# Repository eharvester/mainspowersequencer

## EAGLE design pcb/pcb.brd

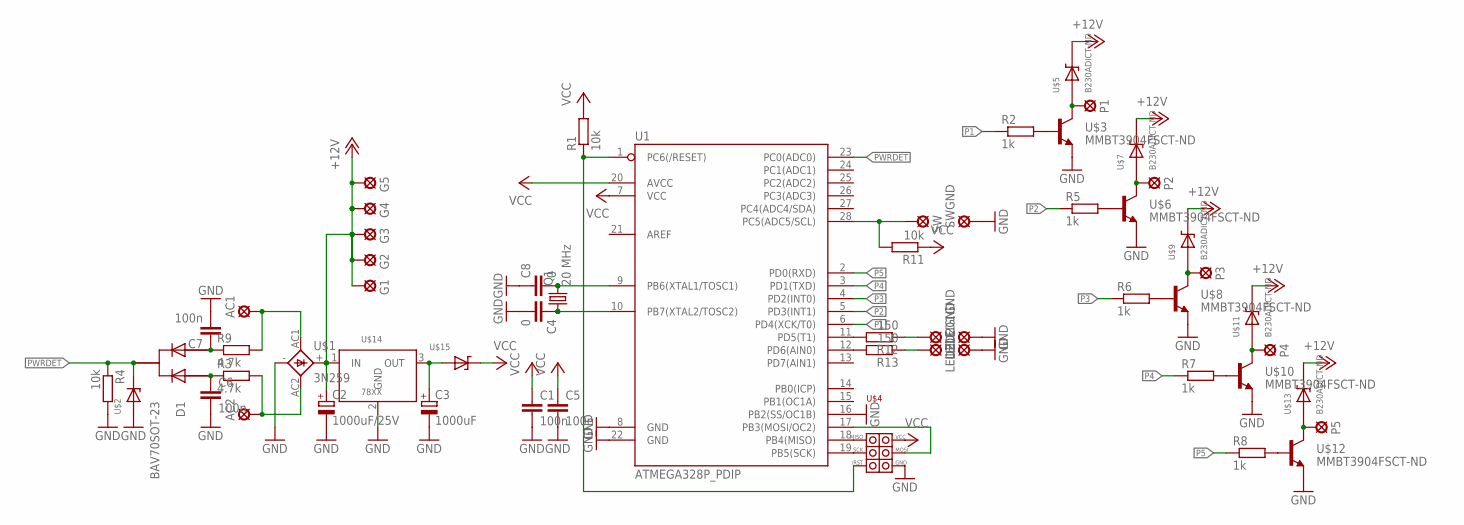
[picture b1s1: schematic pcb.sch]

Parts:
AC1, AC2: LSP10
C1, C5, C6, C7: 100n; C0603
C2: 1000uF/25V; E5-13
C3: 1000uF; E5-10,5
C4, C8: 0; C0603
D1: BAV70SOT-23; SOT23
G1, G2, G3, G4, G5: LSP10
LED1, LED1GND, LED2, LED2GND: LSP10
P1, P2, P3, P4, P5: LSP10
Q1: 20 MHz; CTS406
R1, R4, R11: 10k; R0603
R2, R5, R6, R7, R8: 1k; R0603
R3, R9: 4.7k; R0603
R12, R13: 150; R0603
SW: LSP10
SWGND: LSP10
U1: ATMEGA328P_PDIP; DIL28-3
U$1: 3N259; KBPM
U$2: MA8051CT; SOD323-W
U$3, U$6, U$8, U$10, U$12: MMBT3904FSCT-ND; SOT-23
U$4: ISP-HEADER-6; ISPHEADER-6
U$5, U$7, U$9, U$11, U$13: B230ADICT-ND; SMA/SMB
U$14: 78XX; DPAK
U$15: MBRM140T1; CASE457

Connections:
+12V: C2.+, G1.MP, G2.MP, G3.MP, G4.MP, G5.MP, U$1.+, U$5.1 (CAT), U$7.1 (CAT), U$9.1 (CAT), U$11.1 (CAT), U$13.1 (CAT), U$14.1 (IN)
/RST: R1.1, U1.1 (PC6(/RESET)), U$4./RST
AC1: AC1.MP, R9.2, U$1.AC1
AC2: AC2.MP, R3.2, U$1.AC2
LED1: LED1.MP, R12.1
LED2: LED2.MP, R13.1
MISO: U1.18 (PB4(MISO)), U$4.MISO
MOSI: U1.17 (PB3(MOSI/OC2)), U$4.MOSI
unnamed: C8.2, Q1.3 (2), U1.9 (PB6(XTAL1/TOSC1))
unnamed: C6.1, D1.1ANODE (ANODE1), R3.1
unnamed: C4.1, Q1.1, U1.10 (PB7(XTAL2/TOSC2))
unnamed: C3.+, U$14.3 (OUT), U$15.2 (AN)
unnamed: P3.MP, U$8.3 (C), U$9.2 (AN)
unnamed: P2.MP, U$6.3 (C), U$7.2 (AN)
unnamed: R5.2, U$6.1 (B)
unnamed: C7.1, D1.2ANODE (ANODE2), R9.1
unnamed: P5.MP, U$12.3 (C), U$13.2 (AN)
unnamed: R11.2, SW.MP, U1.28 (PC5(ADC5/SCL))
unnamed: R12.2, U1.11 (PD5(T1))
unnamed: R2.2, U$3.1 (B)
unnamed: P1.MP, U$3.3 (C), U$5.2 (AN)
unnamed: P4.MP, U$10.3 (C), U$11.2 (AN)
unnamed: R6.2, U$8.1 (B)
unnamed: R13.2, U1.12 (PD6(AIN0))
unnamed: R7.2, U$10.1 (B)
unnamed: R8.2, U$12.1 (B)
unnamed: C1.2, C2.-, C3.-, C4.2, C5.2, C6.2, C7.2, C8.1, LED1GND.MP, LED2GND.MP, R4.2, SWGND.MP, U1.8 (GND), U1.16 (PB2(SS/OC1B)), U1.22 (GND), U$1.-, U$2.A (AN), U$3.2 (E), U$4.GND, U$6.2 (E), U$8.2 (E), U$10.2 (E), U$12.2 (E), U$14.2 (GND)
P1: R2.1, U1.6 (PD4(XCK/T0))
P2: R5.1, U1.5 (PD3(INT1))
P3: R6.1, U1.4 (PD2(INT0))
P4: R7.1, U1.3 (PD1(TXD))
P5: R8.1, U1.2 (PD0(RXD))
PWRDET: D1.3CATODE (CATODE), R4.1, U1.23 (PC0(ADC0)), U$2.C (CAT)
SCK: U1.19 (PB5(SCK)), U$4.SCK
VCC: C1.1, C5.1, R1.2, R11.1, U1.7 (VCC), U1.20 (AVCC), U$4.VCC, U$15.1 (CAT)

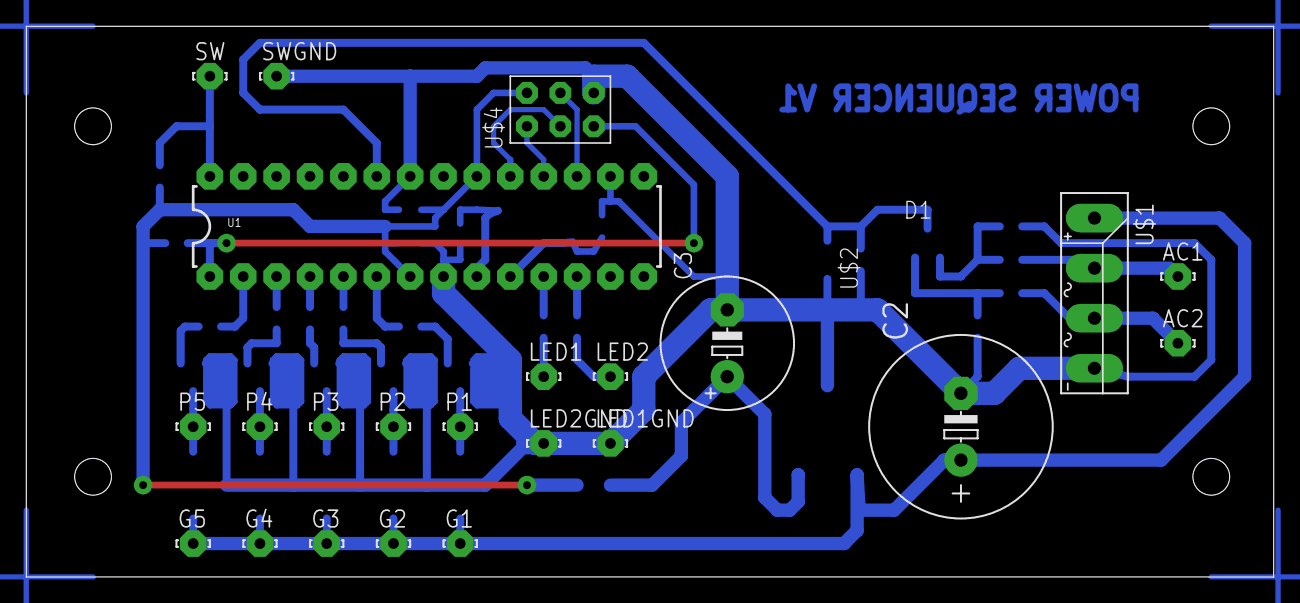
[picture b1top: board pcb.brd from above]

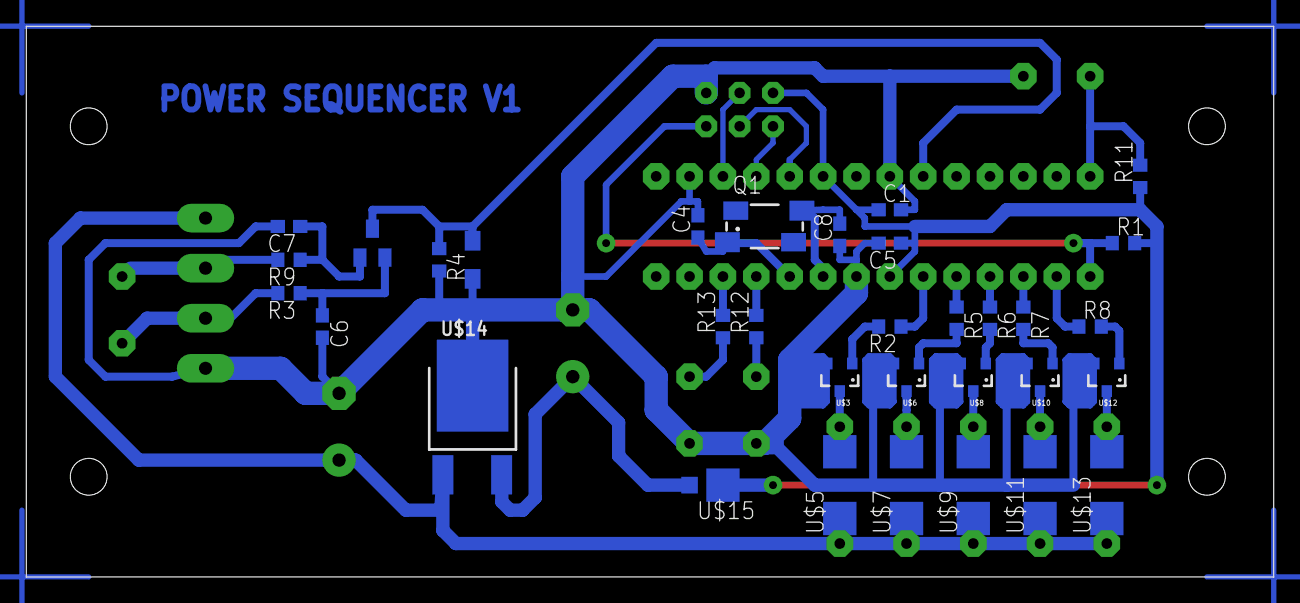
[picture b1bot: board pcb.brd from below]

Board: 2 copper layers, 94.9 x 41.9 mm, 56 parts (31 on the bottom side), 35 nets.

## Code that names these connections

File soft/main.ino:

#define RELAY_CALIBRATION 0

// DIP28 pin# <> Arduino
//  1 A6
//  2 D0 
//  3 D1
//  4 D2
//  5 D3 
//  6 D4
//  7 VCC
//  8 GND
//  9 X1
// 10 X2
// 11 D5
// 12 D6 
// 13 D7
// 14 D8
// 15 D9 
// 16 D10
// 17 D11
// 18 D12
// 19 D13
// 20 AVCC
// 21 AREF
// 22 GND
// 23 A0
// 24 A1
// 25 A2 
// 26 A3
// 27 A4
// 28 A5 


// PCB PIN names
#define LED1 5 // 11
#define LED2 6 // 12

#define P1 4 //6
#define P2 3 //5
#define P3 2 //4
#define P4 1 //3
#define P5 0 //2

#define SW A5 // 28

#define PWRDET A0 // 23

// software pin names

#define BASSAMP P5
#define MIDAMP P4
#define TWEETAMP P3
#define XOVER P2
#define PREAMP P1

#define LEFTLED LED2
#define RIGHTLED LED1

#define PWRBUTTON SW

#define ACSENSE PWRDET 


//relay compensations values in us to achieve zero crossing switching
#define BASSAMP_ON_DELAY 6500 
#define BASSAMP_OFF_DELAY 1600

#define MIDAMP_ON_DELAY 6500 
#define MIDAMP_OFF_DELAY 8200

#define TWEETAMP_ON_DELAY 6600 
#define TWEETAMP_OFF_DELAY 6400

#define XOVER_ON_DELAY 6500 
#define XOVER_OFF_DELAY 1900

#define PREAMP_ON_DELAY 6700 
#define PREAMP_OFF_DELAY 1900


// control macros
#define delus delayMicroseconds

#define BASSAMP_ON {AcSense(); delus(BASSAMP_ON_DELAY); digitalWrite(BASSAMP, 1);}   
#define BASSAMP_OFF {AcSense(); delus(BASSAMP_OFF_DELAY); digitalWrite(BASSAMP, 0);}  

#define MIDAMP_ON {AcSense(); delus(MIDAMP_ON_DELAY); digitalWrite(MIDAMP, 1);}    
#define MIDAMP_OFF {AcSense(); delus(MIDAMP_OFF_DELAY); digitalWrite(MIDAMP, 0);} 

#define TWEETAMP_ON {AcSense(); delus(TWEETAMP_ON_DELAY); digitalWrite(TWEETAMP, 1);}   
#define TWEETAMP_OFF {AcSense(); delus(TWEETAMP_OFF_DELAY); digitalWrite(TWEETAMP, 0);}  

#define XOVER_ON {AcSense(); delus(XOVER_ON_DELAY); digitalWrite(XOVER, 1);}   
#define XOVER_OFF {AcSense(); delus(XOVER_OFF_DELAY); digitalWrite(XOVER, 0);}   

#define PREAMP_ON {AcSense(); delus(PREAMP_ON_DELAY); digitalWrite(PREAMP, 1);} 
#define PREAMP_OFF {AcSense(); delus(PREAMP_OFF_DELAY); digitalWrite(PREAMP, 0);}  


#define LEFTLED_ON digitalWrite(LEFTLED, 1)
#define LEFTLED_OFF digitalWrite(LEFTLED, 0) 

#define RIGHTLED_ON digitalWrite(RIGHTLED, 1) 
#define RIGHTLED_OFF digitalWrite(RIGHTLED, 0) 

#define LEDS_ON {LEFTLED_ON; RIGHTLED_ON;}
#define LEDS_OFF {LEFTLED_OFF; RIGHTLED_OFF;}

unsigned int FlashLedCnt=0;

#define FLASHPERIODSLOW 100
#define FlashLedsSlow {if (FlashLedCnt>=FLASHPERIODSLOW) {FlashLedCnt=0;LEDS_ON;} else {FlashLedCnt++;LEDS_OFF;}}

#define FLASHPERIODALT 8
#define FLASHPERIODALT_H 4
#define FlashLedsAlt {if (FlashLedCnt>=FLASHPERIODALT) {FlashLedCnt=0;LEDS_OFF} else if (FlashLedCnt<FLASHPERIODALT_H) {FlashLedCnt++;LEFTLED_ON;RIGHTLED_OFF;} else {FlashLedCnt++;LEFTLED_OFF;RIGHTLED_ON;}}

// timing definitions
// tick 30 ms (relay cycle consumes max ~16 ms) 
#define TICKS_MS 30UL
// auto off after 8 h 
#define AUTOOFF_MS 28800000UL

// button sensing in 30ms ticks
// push >= 150ms
#define KEYSTABLEMIN 5
// hold >= 600ms
#define KEYSTABLELONGMIN 20 

// power sequence steps in 30ms
#define PWRUPTIME 33
#define PWRDOWNTIME 20


// waits on rising edge of AC power
void AcSense(void) {
 cli();
 while (digitalRead(ACSENSE));
 while (!digitalRead(ACSENSE));
 sei();
}


// FSMs
// control FSM
#define INIT 0
#define PWROFF 1
#define PREAMPON 2
#define XOVERON 3
#define TWEETON 4
#define MIDON 5 
#define BASSON 6
#define PREAMPOFF 7 
#define XOVEROFF 8
#define TWEETOFF 9
#define MIDOFF 10
#define BASSOFF 11
#define SPEAKER 12
#define HEADPHONES 13
byte PwrSqFsm = INIT;


// button FSM
#define UNKNOWN 0
#define OFF 1
#define ON 2
#define LONGON 3
byte ButtonFsm = UNKNOWN;


int Ticks = 0;

unsigned int keyopensample = 0;
unsigned int keyclosedsample = 0;

unsigned long ThenMs;
unsigned long PowerOnTimeMs;

void setup() 
{ 

 pinMode(ACSENSE,INPUT);

 digitalWrite(LED1, 0);   
 digitalWrite(LED2, 0);   
 digitalWrite(P1, 0);   
 digitalWrite(P2, 0);   
 digitalWrite(P3, 0);   
 digitalWrite(P4, 0);   
 digitalWrite(P5, 0);   

 
 pinMode(LED1, OUTPUT);   
 pinMode(LED2, OUTPUT);   
 pinMode(P1, OUTPUT);   
 pinMode(P2, OUTPUT);   
 pinMode(P3, OUTPUT);   
 pinMode(P4, OUTPUT);   
 pinMode(P5, OUTPUT);   
 
 ThenMs = millis();

} 


void loop() 
{ 


#if RELAY_CALIBRATION==1
 LEFTLED_ON; RIGHTLED_ON;
 PREAMP_ON; AcSense();AcSense();AcSense(); PREAMP_OFF; delay(100);

 XOVER_ON; AcSense();AcSense();AcSense(); XOVER_OFF;  delay(100);

 TWEETAMP_ON; AcSense();AcSense(); AcSense(); TWEETAMP_OFF; delay(100);

 MIDAMP_ON; AcSense();AcSense();AcSense(); MIDAMP_OFF; delay(100);
 
 BASSAMP_ON; AcSense();AcSense();AcSense(); BASSAMP_OFF; delay(100);
 LEFTLED_OFF; RIGHTLED_OFF;
 delay(1000);

#else
 byte sample; 
 unsigned long NowMs = millis();

// FSM
 switch (PwrSqFsm) {
  case INIT:
   LEDS_OFF;
   if (ButtonFsm==OFF) PwrSqFsm = PWROFF;
   break;

  case PWROFF:
   FlashLedsSlow;
   if (ButtonFsm==ON) {PREAMP_ON; PwrSqFsm = PREAMPON; PowerOnTimeMs = ThenMs;}
   break;

  case PREAMPON:
   FlashLedsAlt;
   if (Ticks == PWRUPTIME) {Ticks = 0; if (ButtonFsm==LONGON) PwrSqFsm = HEADPHONES; else {XOVER_ON; PwrSqFsm = XOVERON;}}
   else Ticks++;
   break;

  case HEADPHONES:
   LEFTLED_ON; RIGHTLED_OFF;
   if ((ButtonFsm==ON) || ((unsigned long)(ThenMs-PowerOnTimeMs) >= AUTOOFF_MS)) {PREAMP_OFF; PwrSqFsm = PREAMPOFF;}
   break;

  case XOVERON:
   FlashLedsAlt;
   if (Ticks == PWRUPTIME) {Ticks=0; TWEETAMP_ON; PwrSqFsm = TWEETON;}
   else Ticks++;
   break;

  case TWEETON:
   FlashLedsAlt;
   if (Ticks == PWRUPTIME) {Ticks=0; MIDAMP_ON; PwrSqFsm = MIDON;}
   else Ticks++;
   break;

  case MIDON:
   FlashLedsAlt;
   if (Ticks == PWRUPTIME) {Ticks=0; BASSAMP_ON; PwrSqFsm = BASSON;}
   else Ticks++;
   break;

  case BASSON:
   FlashLedsAlt;
    if (Ticks == PWRUPTIME) {Ticks=0; PwrSqFsm = SPEAKER;}
    else Ticks++;
   break;

  case SPEAKER:
   LEDS_ON;
   if ((ButtonFsm==ON) || ((unsigned long)(ThenMs-PowerOnTimeMs) >= AUTOOFF_MS)) {TWEETAMP_OFF; PwrSqFsm = TWEETOFF;} 
   break;

  case TWEETOFF:
   FlashLedsAlt;
   if (Ticks == PWRDOWNTIME) {Ticks=0; MIDAMP_OFF; PwrSqFsm = MIDOFF;}
   else Ticks++;
   break;
        
  case MIDOFF:
   FlashLedsAlt;
  if (Ticks == PWRDOWNTIME) {Ticks=0; BASSAMP_OFF; PwrSqFsm = BASSOFF;}
   else Ticks++;
   break;       

  case BASSOFF:
   FlashLedsAlt;
   if (Ticks == PWRDOWNTIME) {Ticks=0; XOVER_OFF; PwrSqFsm = XOVEROFF;}
   else Ticks++;
   break;  
  
  case XOVEROFF:
   FlashLedsAlt;
   if (Ticks == PWRDOWNTIME) {Ticks = 0; if (ButtonFsm==LONGON) {PwrSqFsm = HEADPHONES; PowerOnTimeMs = ThenMs;} else {PREAMP_OFF; PwrSqFsm = PREAMPOFF;}}
   else Ticks++;
   break;  

  case PREAMPOFF:
   FlashLedsAlt;
   if (Ticks == PWRDOWNTIME) {Ticks=0; PwrSqFsm = INIT;}
   else Ticks++;
   break;  

  default: 
   break;
 } // switch      


// Button FSM
 switch (ButtonFsm) {
  case UNKNOWN:
   if (keyopensample >= KEYSTABLEMIN) ButtonFsm = OFF;
  case OFF: 
   if (keyclosedsample >= KEYSTABLEMIN) ButtonFsm = ON;
  case ON:
   if (keyclosedsample >= KEYSTABLELONGMIN) ButtonFsm = LONGON;
  case LONGON:
   if (keyopensample >= KEYSTABLEMIN) ButtonFsm = OFF;
 }
// sense button
 sample = digitalRead(PWRBUTTON);
 keyopensample = sample?(keyopensample<KEYSTABLEMIN)?keyopensample+1:keyopensample:0; // low active key
 keyclosedsample = sample?0:(keyclosedsample<KEYSTABLELONGMIN)?keyclosedsample+1:keyclosedsample; // low active key

// wait on next TICKS_MS period
 do {NowMs = millis();} while ((unsigned long)(NowMs - ThenMs) < TICKS_MS);
 ThenMs = millis();

#endif
} 

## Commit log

2019-01-14 fix Makefile
